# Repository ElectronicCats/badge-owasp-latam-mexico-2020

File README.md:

# Badge OWASP LATAM México 2020

Una vez mas en el año 2020 nos reunimos para celebrar OWASP Latam México 2020, en Electronic Cats hemos creado un badge electronico para todos los asistentes, bienvenidos a la #badgelive

## Capture The Flag

Unete al reto de Capture The Flag y descubre todo lo que tiene dentro este badge por medio de una herramienta Bluetooth ;)

## Tecnologia

- ESP32 BLE and WIFI
- Convetidor USB-Serial
- LED WS2812B Mini
- OLED
  - [Version 1](https://uelectronics.com/producto/display-pantalla-oled-blanco-128x32-0-91-i2c-ssd1306/)
  - [Version 2](https://articulo.mercadolibre.com.mx/MLM-878713326-display-pantalla-oled-128x32-091-arduino-pic-i2c-lcd-_JM#position=1&search_layout=grid&type=pad&tracking_id=39be533f-0b75-4b89-943c-e1481425476c&is_advertising=true&ad_domain=VQCATCORE_LST&ad_position=1&ad_click_id=NjJlMjUyZGItODc5Zi00ODY1LWIwYTgtNjJlMTVmOGMyMGRm)

## Links

- [ESP32 con Arduino](https://github.com/espressif/arduino-esp32)
- [Herramienta para carga de binario CTF](https://github.com/espressif/esptool)

## Agradecimientos
¿Quieres dar las gracias? Etiqueta a estas empresas en redes sociales y muestrales tu badge, gracias a ellos es posible

- [PCBWay](https://www.pcbway.com/)
- [LCSC](https://lcsc.com/)
- [ESPRESSIF](https://www.espressif.com/)

## License

Electronic Cats invests time and resources providing this open source design, please support Electronic Cats and open-source hardware by purchasing products from Electronic Cats!

Designed by Electronic Cats.

Hardware released under an CERN Open Hardware Licence v1.2. See the LICENSE_HARDWARE file for more information.

Electronic Cats is a registered trademark, please do not use if you sell these PCBs.

Dec 2019

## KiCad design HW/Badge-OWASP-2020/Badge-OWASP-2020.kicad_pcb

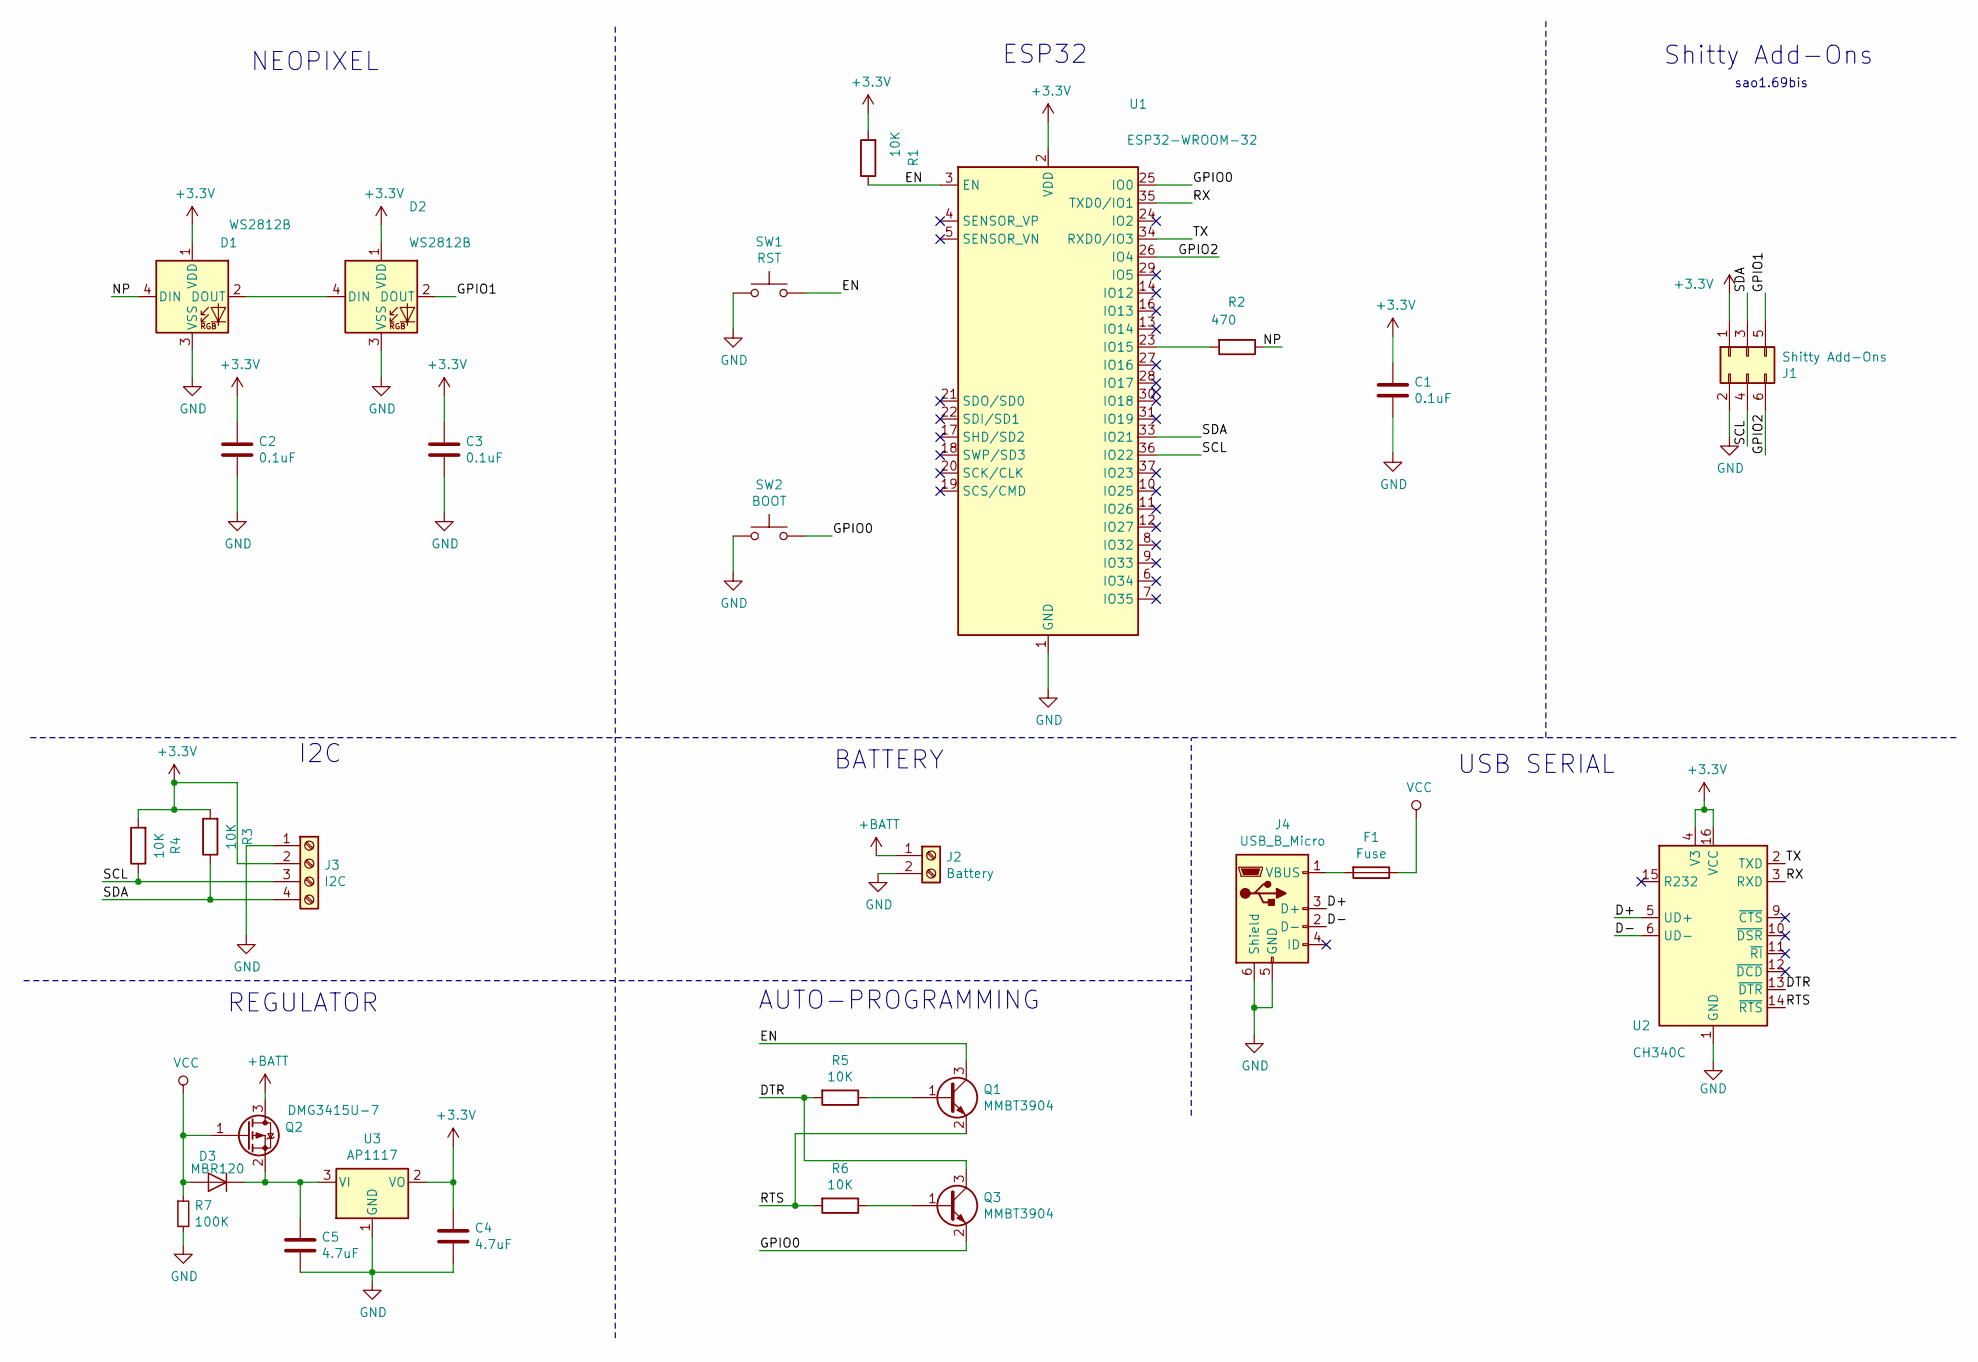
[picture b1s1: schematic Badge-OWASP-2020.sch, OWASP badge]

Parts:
C1, C2, C3: 0.1uF; C_0805_2012Metric_Pad1.15x1.40mm_HandSolder
C4, C5: 4.7uF; C_0805_2012Metric_Pad1.15x1.40mm_HandSolder
D1, D2: WS2812B; LED_SK6812MINI_PLCC4_3.5x3.5mm_P1.75mm
D3: MBR120; D_SOD-123F
F1: Fuse; Fuse_1812_4532Metric_Pad1.30x3.40mm_HandSolder
J1: Shitty Add-Ons; PinHeader_2x03_P2.54mm_Vertical
J2: Battery; PinHeader_1x02_P2.54mm_Vertical
J3: I2C; PinHeader_1x04_P2.54mm_Vertical
J4: USB_B_Micro; U254051N4BH806
Q1, Q3: MMBT3904; SOT-23
Q2: DMG3415U-7; SOT-23
R1, R3, R4, R5, R6: 10K; R_0805_2012Metric_Pad1.15x1.40mm_HandSolder
R2: 470; R_0805_2012Metric_Pad1.15x1.40mm_HandSolder
R7: 100K; R_0805_2012Metric_Pad1.15x1.40mm_HandSolder
SW1: RST; SW_SPST_TL3342
SW2: BOOT; SW_SPST_TL3342
U1: ESP32-WROOM-32
U2: CH340C; SOIC-16_3.9x9.9mm_P1.27mm
U3: AP1117; SOT-223-3_TabPin2

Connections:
+3V3: C1.1, C2.1, C3.1, C4.1, D1.1 (VDD), D2.1 (VDD), J1.1, J3.2, R1.2, R3.2, R4.2, U1.2 (VDD), U2.4 (V3), U2.16 (VCC), U3.2 (VO)
+BATT: J2.1, Q2.3 (D)
/D+: J4.3 (D+), U2.5 (UD+)
/D-: J4.2 (D-), U2.6 (UD-)
/DTR: Q3.3 (C), R5.2, U2.13 (~DTR)
/EN: Q1.3 (C), R1.1, SW1.2, U1.3 (EN)
/GPIO0: Q3.2 (E), SW2.2, U1.25 (IO0)
/GPIO1: D2.2 (DOUT), J1.5
/GPIO2: J1.6, U1.26 (IO4)
/NP: D1.4 (DIN), R2.1
/RTS: Q1.2 (E), R6.2, U2.14 (~RTS)
/RX: U1.35 (TXD0/IO1), U2.3 (RXD)
/SCL: J1.4, J3.3, R4.1, U1.36 (IO22)
/SDA: J1.3, J3.4, R3.1, U1.33 (IO21)
/TX: U1.34 (RXD0/IO3), U2.2 (TXD)
GND: C1.2, C2.2, C3.2, C4.2, C5.2, D1.3 (VSS), D2.3 (VSS), J1.2, J2.2, J3.1, J4.5 (GND), J4.6 (Shield), R7.2, SW1.1, SW2.1, U1.1 (GND), U1.15 (GND), U1.38 (GND), U2.1 (GND), U3.1 (GND)
unnamed: C5.1, D3.1 (K), Q2.2 (S), U3.3 (VI)
unnamed: D1.2 (DOUT), D2.4 (DIN)
unnamed: F1.2, J4.1 (VBUS)
unnamed: Q1.1 (B), R5.1
unnamed: Q3.1 (B), R6.1
unnamed: R2.2, U1.23 (IO15)
VCC: D3.2 (A), F1.1, Q2.1 (G), R7.1

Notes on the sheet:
NEOPIXEL
ESP32
REGULATOR
USB SERIAL
AUTO-PROGRAMMING
I2C
BATTERY
Shitty Add-Ons
sao1.69bis

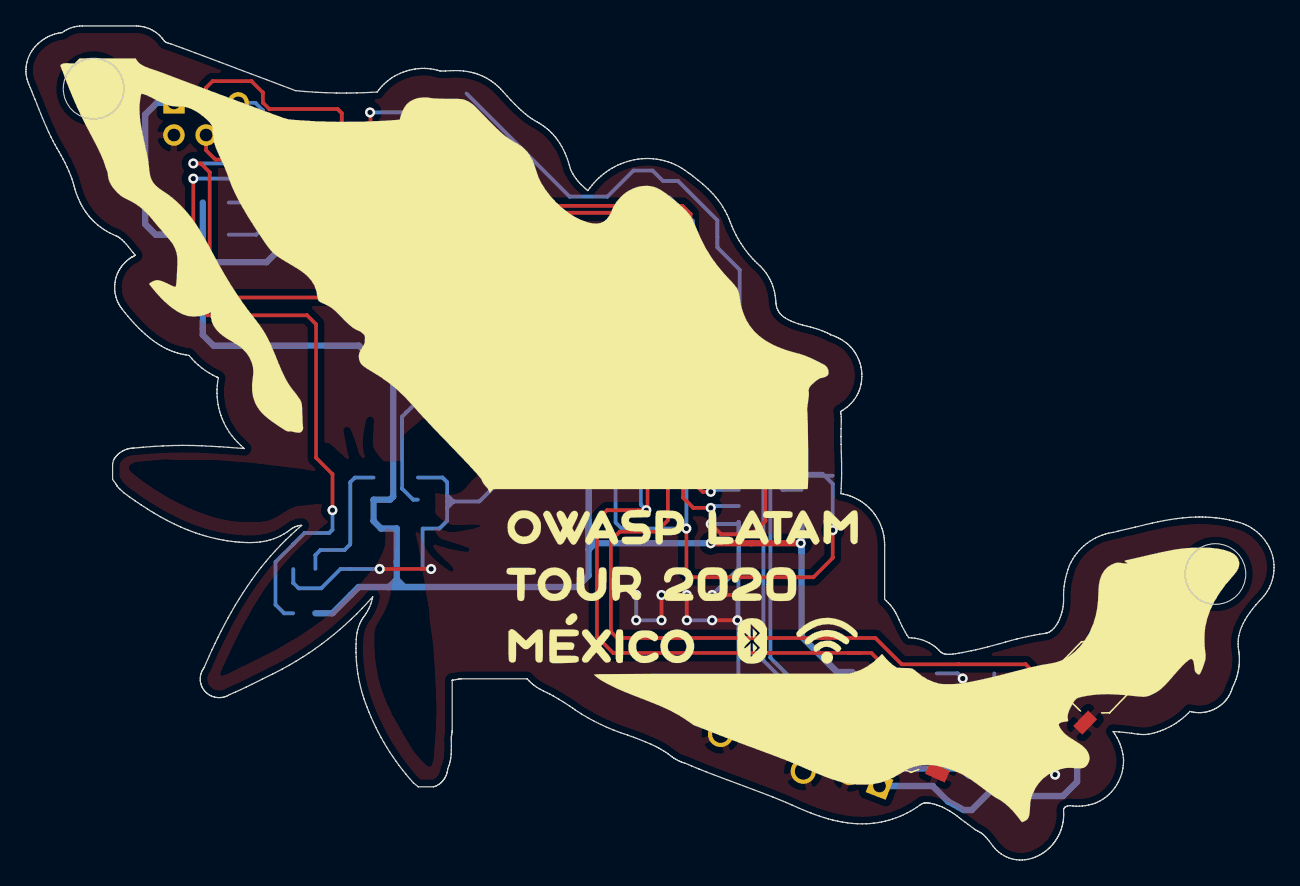
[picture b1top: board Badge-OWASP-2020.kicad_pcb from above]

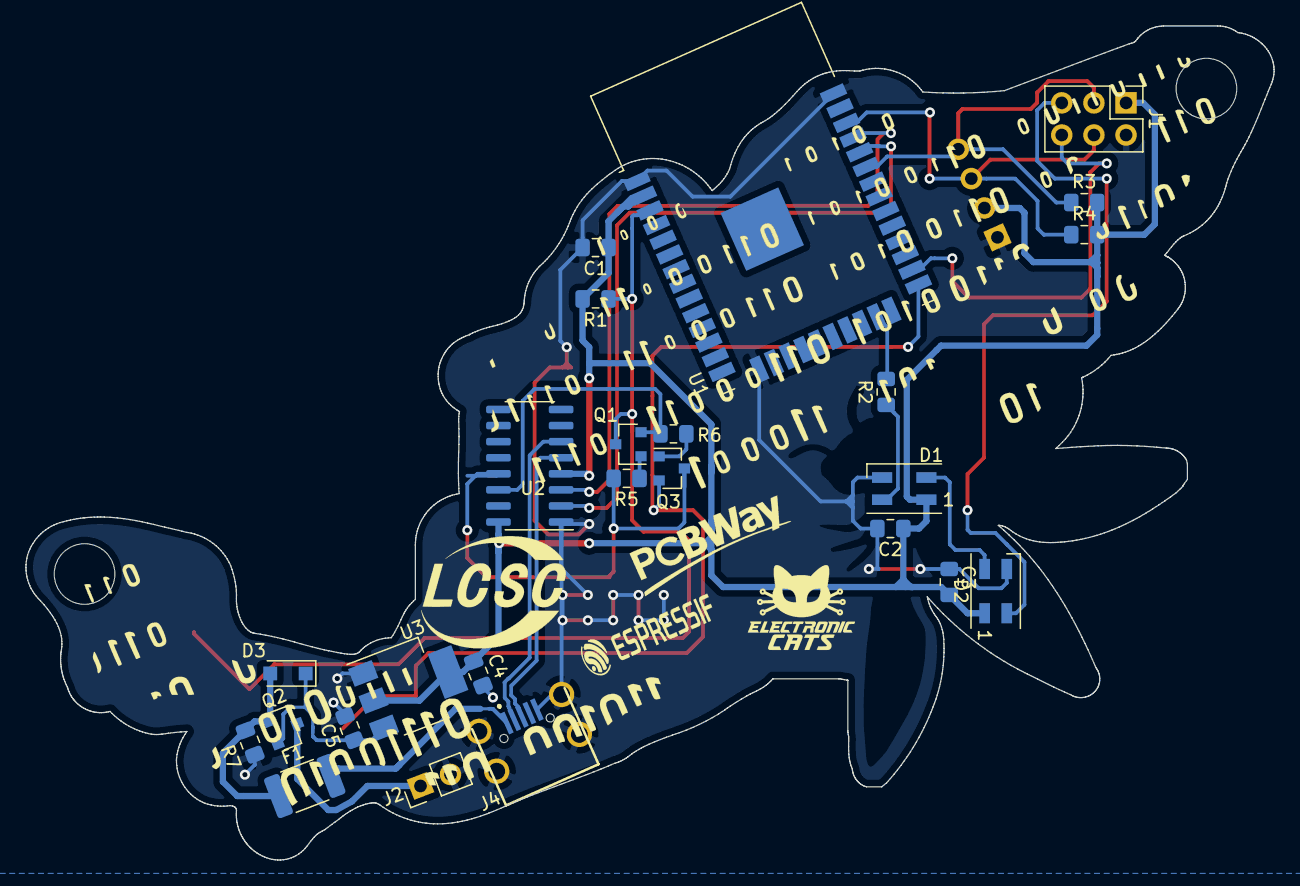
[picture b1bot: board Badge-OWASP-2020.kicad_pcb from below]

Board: 2 copper layers, 98.6 x 65.9 mm, 29 parts (25 on the bottom side), 23 nets.

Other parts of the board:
Ref**: Val**; Badge_2020_OWASP

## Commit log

2019-12-12 CH340C and AP111733
2019-12-12 Add MMBT3904
2019-12-13 Change RTS
2019-12-13 C and GND WS2812B
2019-12-13 Values C and R
2019-12-13 Screen OLED
2019-12-14 ESP32
2019-12-16 Create LICENSE_HARDWARE
2019-12-19 footprints
2019-12-20 Change footprints and add R
2019-12-20 add labels and fix voltage
2019-12-20 add gitignore
2019-12-24 add battery and protection
2019-12-24 Update labels
2019-12-27 fix GPIO1 for shitty adons with neopixel
2019-12-27 correct pinout sao1.69bis
2020-01-02 Add manf#
2020-01-06 fix names tx and rx drc
2020-01-08 define design :D
2020-01-08 update svg
2020-01-10 component distribution
2020-01-10 countour circle
2020-01-10 logos space
2020-01-10 add logos
2020-01-10 fix logos
2020-01-10 Add USB connector from LCSC change angle of components
2020-01-11 routeo
2020-01-12 routeo gnd
2020-01-12 Update traces and ground plane
2020-01-12 add keepout areas :D
2020-01-12 add config pcb gerbers
2020-01-29 Update buttons
2020-03-04 add firmware test oled and nepixels
2020-03-04 PCB v1.0
2021-07-09 Agregando el README y binario del CTF para el badge
2021-07-14 Se corrgio el valor de la primera bandera
2021-07-17 Se corrigio el password de la red WiFi
2021-08-16 Update README.md
    Error de capitalizacion en `write_Flash`. La leta `F` tiene que ir en minusculas.
2021-08-16 Update README.md
    Se modifico el `write_Flash` de linux. La letra `F` debe ir en minusculas
2021-09-05 Código fuente del CTF
2026-05-11 Fix: Correccion a logos / funcionalidad
2026-05-11 Fix: Correcion de inicializacion
